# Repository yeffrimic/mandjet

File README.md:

# mandjet
Placa de control de servos y motores dc usando xiao esp32c3

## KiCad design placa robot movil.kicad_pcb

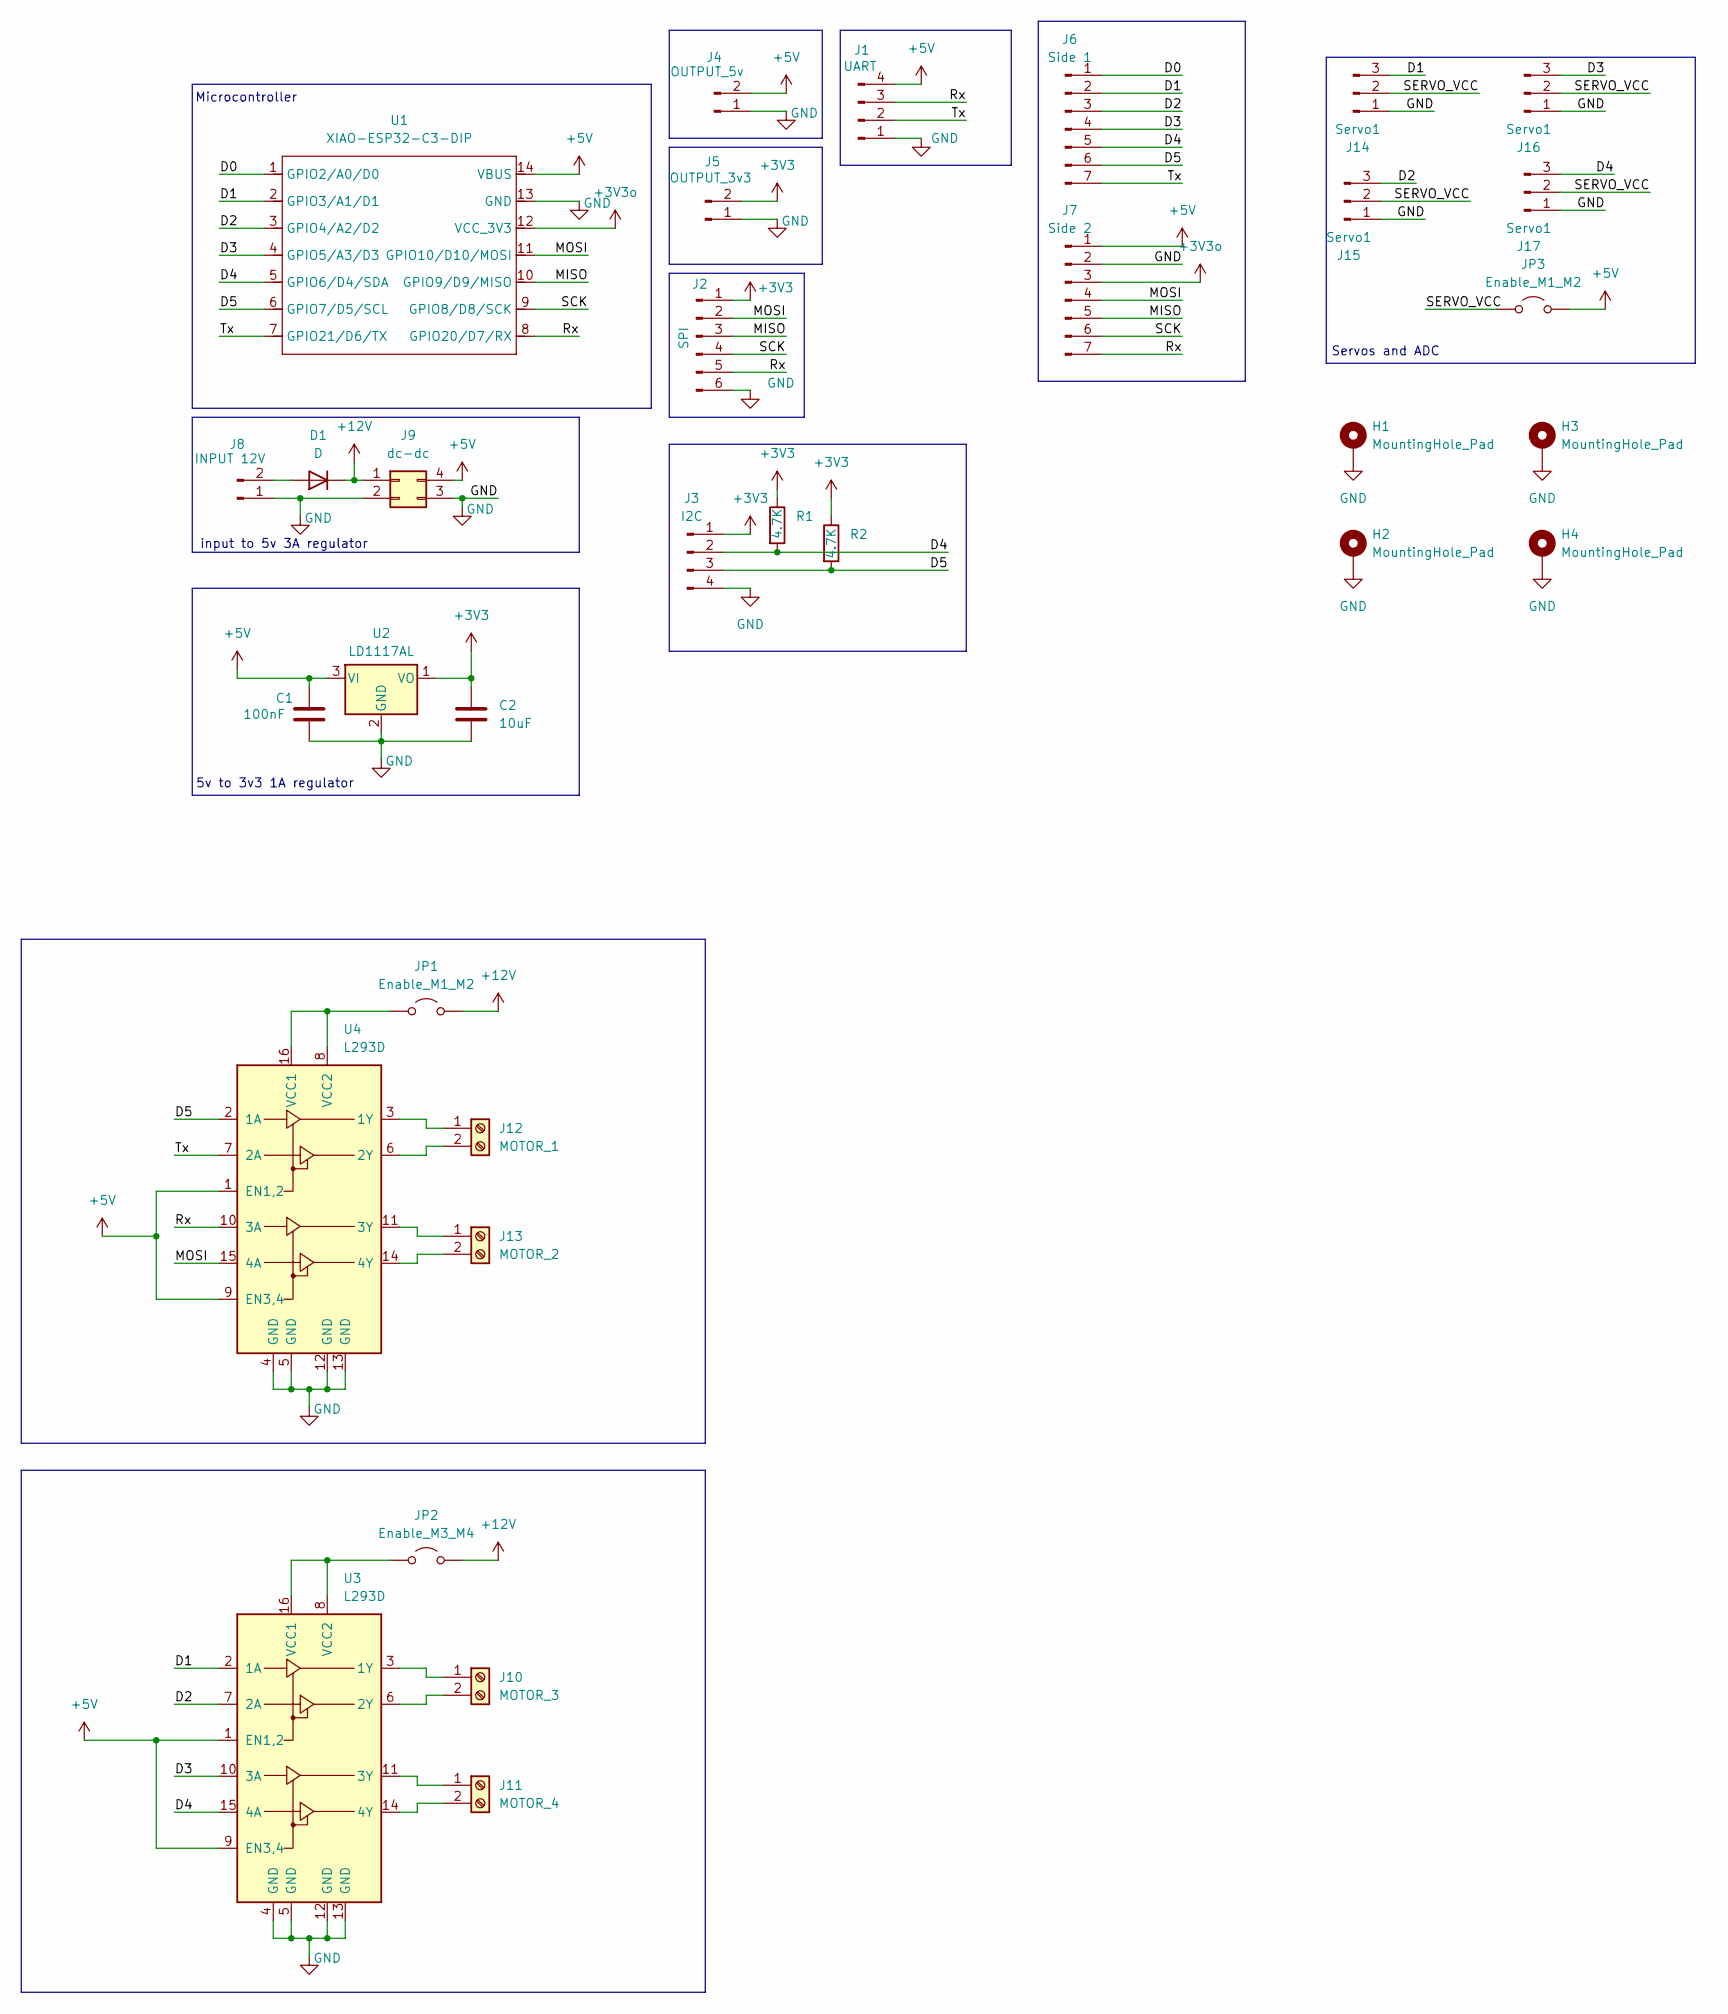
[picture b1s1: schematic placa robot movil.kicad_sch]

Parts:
C1: 100nF; C_Disc_D3.0mm_W1.6mm_P2.50mm
C2: 10uF; CP_Radial_D5.0mm_P2.50mm
D1: D; D_DO-41_SOD81_P7.62mm_Horizontal
H1, H2, H3, H4: MountingHole_Pad; MountingHole_3.5mm_Pad
J1: UART; PinHeader_1x04_P2.54mm_Vertical
J2: SPI; PinHeader_1x06_P2.54mm_Vertical
J3: I2C; PinHeader_1x04_P2.54mm_Vertical
J4: OUTPUT_5v; PinHeader_1x02_P2.54mm_Vertical
J5: OUTPUT_3v3; PinHeader_1x02_P2.54mm_Vertical
J6: Side 1; PinHeader_1x07_P2.54mm_Vertical
J7: Side 2; PinHeader_1x07_P2.54mm_Vertical
J8: INPUT 12V; TerminalBlock_Phoenix_MKDS-1,5-2_1x02_P5.00mm_Horizontal
J9: dc-dc; YAAJ_DCDC_StepDown_LM2596
J10: MOTOR_3; TerminalBlock_Phoenix_MKDS-1,5-2_1x02_P5.00mm_Horizontal
J11: MOTOR_4; TerminalBlock_Phoenix_MKDS-1,5-2_1x02_P5.00mm_Horizontal
J12: MOTOR_1; TerminalBlock_Phoenix_MKDS-1,5-2_1x02_P5.00mm_Horizontal
J13: MOTOR_2; TerminalBlock_Phoenix_MKDS-1,5-2_1x02_P5.00mm_Horizontal
J14, J15, J16, J17: Servo1; PinHeader_1x03_P2.54mm_Vertical
JP1, JP3: Enable_M1_M2; PinHeader_1x02_P2.54mm_Vertical
JP2: Enable_M3_M4; PinHeader_1x02_P2.54mm_Vertical
R1, R2: 4.7K; R_Axial_DIN0207_L6.3mm_D2.5mm_P10.16mm_Horizontal
U1: XIAO-ESP32-C3-DIP; XIAO-ESP32C3-DIP
U2: LD1117AL; TO-220-3_Vertical
U3, U4: L293D; DIP-16_W7.62mm

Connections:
+3V3: C2.1, J2.1, J3.1, J5.2, R1.1, R2.1, U2.1 (VO)
+3V3o: J7.3, U1.12 (VCC_3V3)
+5V: C1.1, J1.4, J4.2, J7.1, J9.4, JP3.2 (B), U1.14 (VBUS), U2.3 (VI), U3.1 (EN1,2), U3.9 (EN3,4), U4.1 (EN1,2), U4.9 (EN3,4)
+12V: D1.1 (K), J9.1, JP1.2 (B), JP2.2 (B)
/D0: J6.1, U1.1 (GPIO2/A0/D0)
/D1: J6.2, J14.3, U1.2 (GPIO3/A1/D1), U3.2 (1A)
/D2: J6.3, J15.3, U1.3 (GPIO4/A2/D2), U3.7 (2A)
/D3: J6.4, J16.3, U1.4 (GPIO5/A3/D3), U3.10 (3A)
/D4: J3.2, J6.5, J17.3, R1.2, U1.5 (GPIO6/D4/SDA), U3.15 (4A)
/D5: J3.3, J6.6, R2.2, U1.6 (GPIO7/D5/SCL), U4.2 (1A)
/MISO: J2.3, J7.5, U1.10 (GPIO9/D9/MISO)
/MOSI: J2.2, J7.4, U1.11 (GPIO10/D10/MOSI), U4.15 (4A)
/Rx: J1.3, J2.5, J7.7, U1.8 (GPIO20/D7/RX), U4.10 (3A)
/SCK: J2.4, J7.6, U1.9 (GPIO8/D8/SCK)
/SERVO_VCC: J14.2, J15.2, J16.2, J17.2, JP3.1 (A)
/Tx: J1.2, J6.7, U1.7 (GPIO21/D6/TX), U4.7 (2A)
GND: C1.2, C2.2, H1.1, H2.1, H3.1, H4.1, J1.1, J2.6, J3.4, J4.1, J5.1, J7.2, J8.1, J9.2, J9.3, J14.1, J15.1, J16.1, J17.1, U1.13 (GND), U2.2 (GND), U3.4 (GND), U3.5 (GND), U3.12 (GND), U3.13 (GND), U4.4 (GND), U4.5 (GND), U4.12 (GND), U4.13 (GND)
unnamed: D1.2 (A), J8.2
unnamed: J10.1, U3.3 (1Y)
unnamed: J10.2, U3.6 (2Y)
unnamed: J11.1, U3.11 (3Y)
unnamed: J11.2, U3.14 (4Y)
unnamed: J12.1, U4.3 (1Y)
unnamed: J12.2, U4.6 (2Y)
unnamed: J13.1, U4.11 (3Y)
unnamed: J13.2, U4.14 (4Y)
unnamed: JP1.1 (A), U4.8 (VCC2), U4.16 (VCC1)
unnamed: JP2.1 (A), U3.8 (VCC2), U3.16 (VCC1)

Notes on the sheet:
Microcontroller
input to 5v 3A regulator
5v to 3v3 1A regulator
Servos and ADC

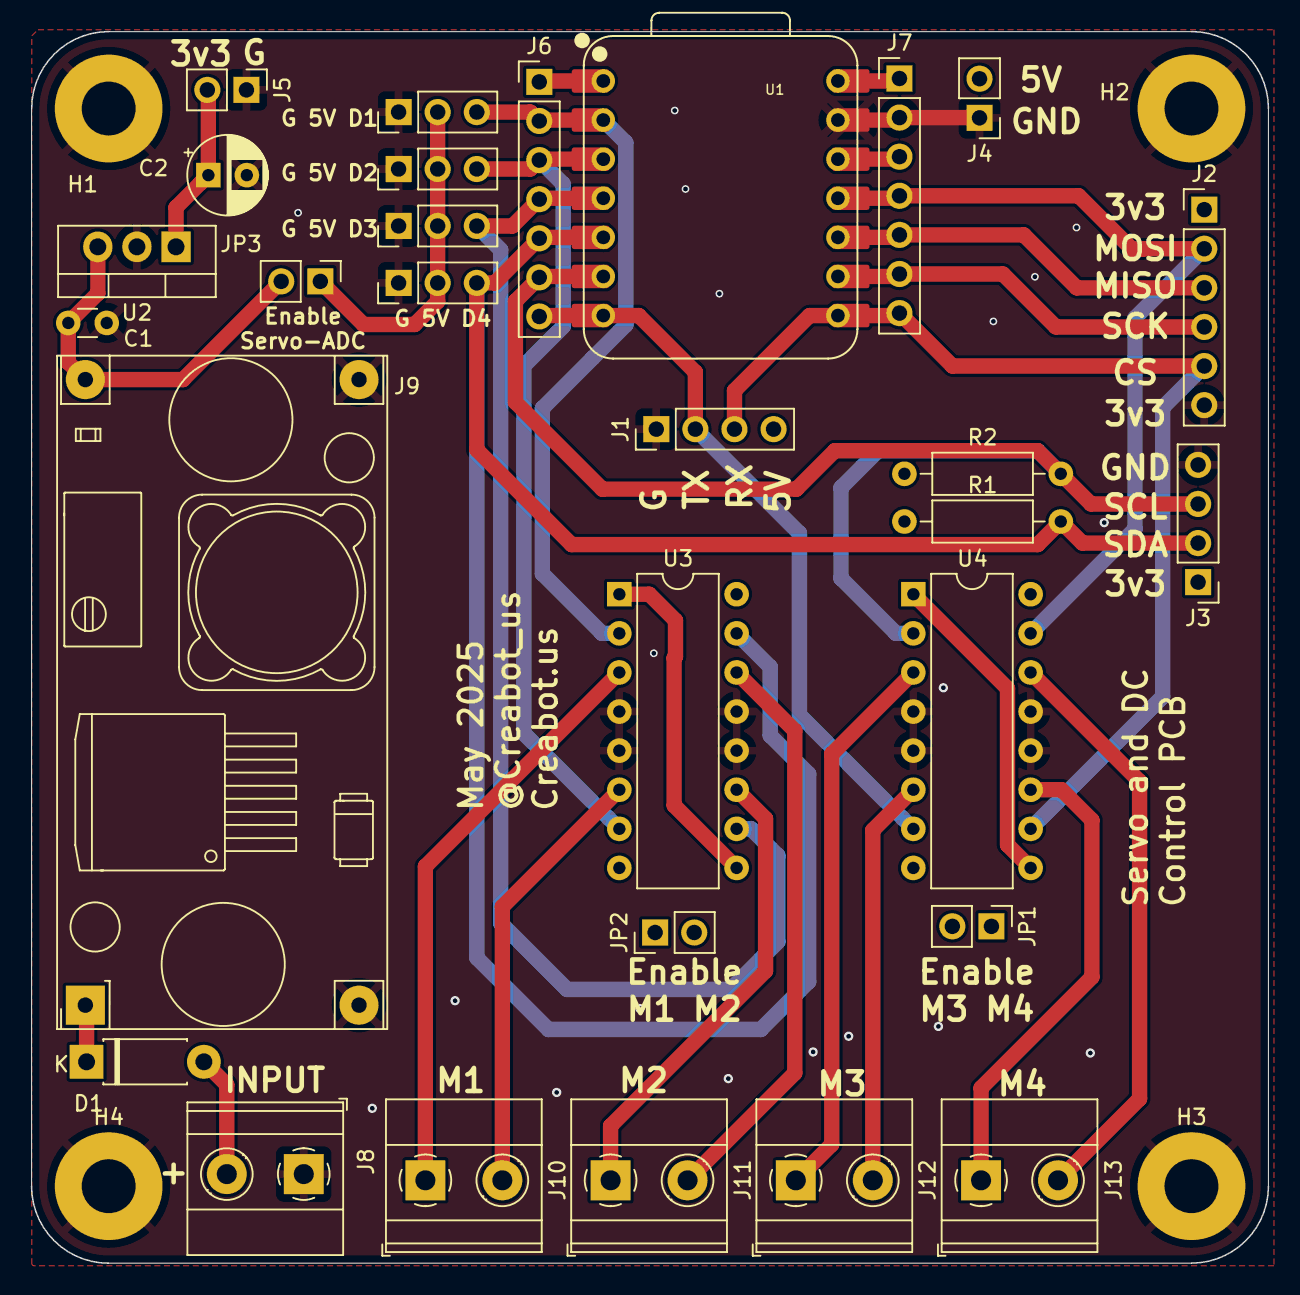
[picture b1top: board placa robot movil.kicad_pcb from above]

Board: 4 copper layers, 80.4 x 80.0 mm, 33 parts (0 on the bottom side), 28 nets.
